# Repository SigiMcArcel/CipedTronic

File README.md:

#  feasibility study. Bicycle Speedometer
Hardware and software for measuring distance of a bike with a mobil phone.
The needed information will get thru the sine wave of the hub dynamo of the bike.
A hardware converts the sine wave to a TTL signal. 
A microcontroller counts the pulses
The mobil gets the data thru Bluetooth LE
A java app receive the Bluetooth LE data and shows the value on a GUI
The hardware must be simple and small for covering in a bicycle lamp.

#The Application
The microcontroller sends the 

count of pulses (distance), 
the count of pulses per second (velocity)
the count of pulses per second average
the count of pulses per second maximum
The count of pulses will save in the microcontrollers EEPROM

The Android App calculates the informations to Km/h and Km with settings like pulses per revolution and wheel radius,
this data will show in the GUI.

In the first Version i implemented the nordic UART Service and send and receive the data as string.
In the further versions i used a custom service and characteristics to exchange the data.So i spent code and was more comfortable to handle it 

The next idea is to use the standard Bluetooth LE service "Cycling Speed and Cadence" to exchange the data.
So i can use my speedometer with other android Apps.
Therfore i have to reimplement the the pulse measuring.

further steps are :
- Porting the software to a seed XIAO ESP32C3 is lot smaller and has akku load functions
- Combine the hardware with LED Lightning and Supercaps
- extend the android app with "Tours" functionality. So i can set several tours.

##Hardware Komponents
ATMEGA 32u4 Arduino Leonard0
Adafruit nrf80001 breakout
Samsung X-Cover Pro Smartphone Android SDK 30

#Developer Tools
Microchip studio for ATMEGA 32u4
Android studio for Android App developing
LT Spice for developing the Converter Hardware

## Hardware for pulse converting
The big Problem is to handle the voltage on unloaded state.
The voltage can gos up to > 20 Volts.

I'm still looking for a good and sinmplesolution for this problem

##Software
###Microcontroller
Project : CipedTronicMCU
The Software uses fololowing sources:
the nordic nrf80001 sdk
The USB CDC from J. Fiene & J. Romano https://github.com/PennRobotics/acrobot 

USBSerial:
For debugging i implemented a Modul for receive and send string and chars thru the usb interface of the ATMEGA 32u4.
Therfore i'm using the USBDCD source.

Bluetooth LE:
The Atmega 32u4 communicate thru SPI with the Bluetooth LE Breakout.
In the modul BLE.cpp all needed step are implemented for using the breakout.
The nordic sdk includes the necessary functions.
BLE.cpp is written in c++ for compatibility to the nordic sdk.

Evaluate the sine waves of the hub dynamo:
For that i use the counter 1 of the Atmega 32u4. it is count the pulses.
For prevent the overflow after 16 Bit, the software adds the actual counter value to a 32 bit variable and deletes the counter.
Every second the software checks the count of pulses since last call ang gives the count of pulses per second (Counter.c ,Timer.c)

maximum km's:
(Unloaded)
wheel radius = 37 cm, pulses per revolution = 18
circumference per revolution = 2 * 0,00037 kilometers * pi =    0,00232477856 kilometers
pulses per km = 1/0,00232477856 * 18 = 7742 Pulses
or 0,12915436 meters per puls

u32Bit =  4294967295 /7742 = 554761 km. (less than i thought,may be i need a u64Bit Integer)

accuracy:
depends on tire pressure and wight.
Loaded ->
Assumed 4,5 Bar pressure and 70 kg weight a different of 5 mm
circumference per revolution = 2 * 0,000365 kilometers * pi =    0,00229336263 kilometers
pulses per km = 1/0,00229336263 * 18 = 7 848 Pulses
or  0,12740903 meters per pulse									 
unloaded <-> loaded ->
6 Pulses -> 76 cm

almost a metre per kilometre. its a lot !!
But I found a test of gps tracker on Internet. Result : Real distance 5Km , gps tracker 5,14 km.
the speedometer  calculates :  5 km -> 5 * 76 cm = 380 cm. Maybe better.

###Android App
The App is implemented as a Viewmodel Pattern.
The BLE part is implemented fully asynchron. 
Actually the BLE part is written as a singleton class. But it prepared for using as Android service.
The data exchange between class and Viewmodel works with events and livedata.
GUI:
The App consists three Fragments there's is collected as tabs.
Main and Datafragments :
- Shows the velocity and distance
- Resets the counter
Devicefragment:
- Searching and select cipedtronic devices
Settingsfragment:
- Sets wheel raduis and pulses per revolution

classes:
BLEDevice.java : Consist the BLE Stack with all needed functionality.
CipedTronicMCU.java : Opens BLE services,handle characteristics, calculate mcu data
PageViewModel.java : handles data exchange beetween Fragments, starts the MCU/BLE Part

SectionsPagerAdapter.java : Handles Tabs and Fragments
DataFragment.java : The data GUI
DeviceFragment.java : The device search fragment
SettingsFragment.java : The settings fragment

#Branches:
##main
BLE Uart Version of Cipedtronic
##BLENonUart
 the CUstom and standard service

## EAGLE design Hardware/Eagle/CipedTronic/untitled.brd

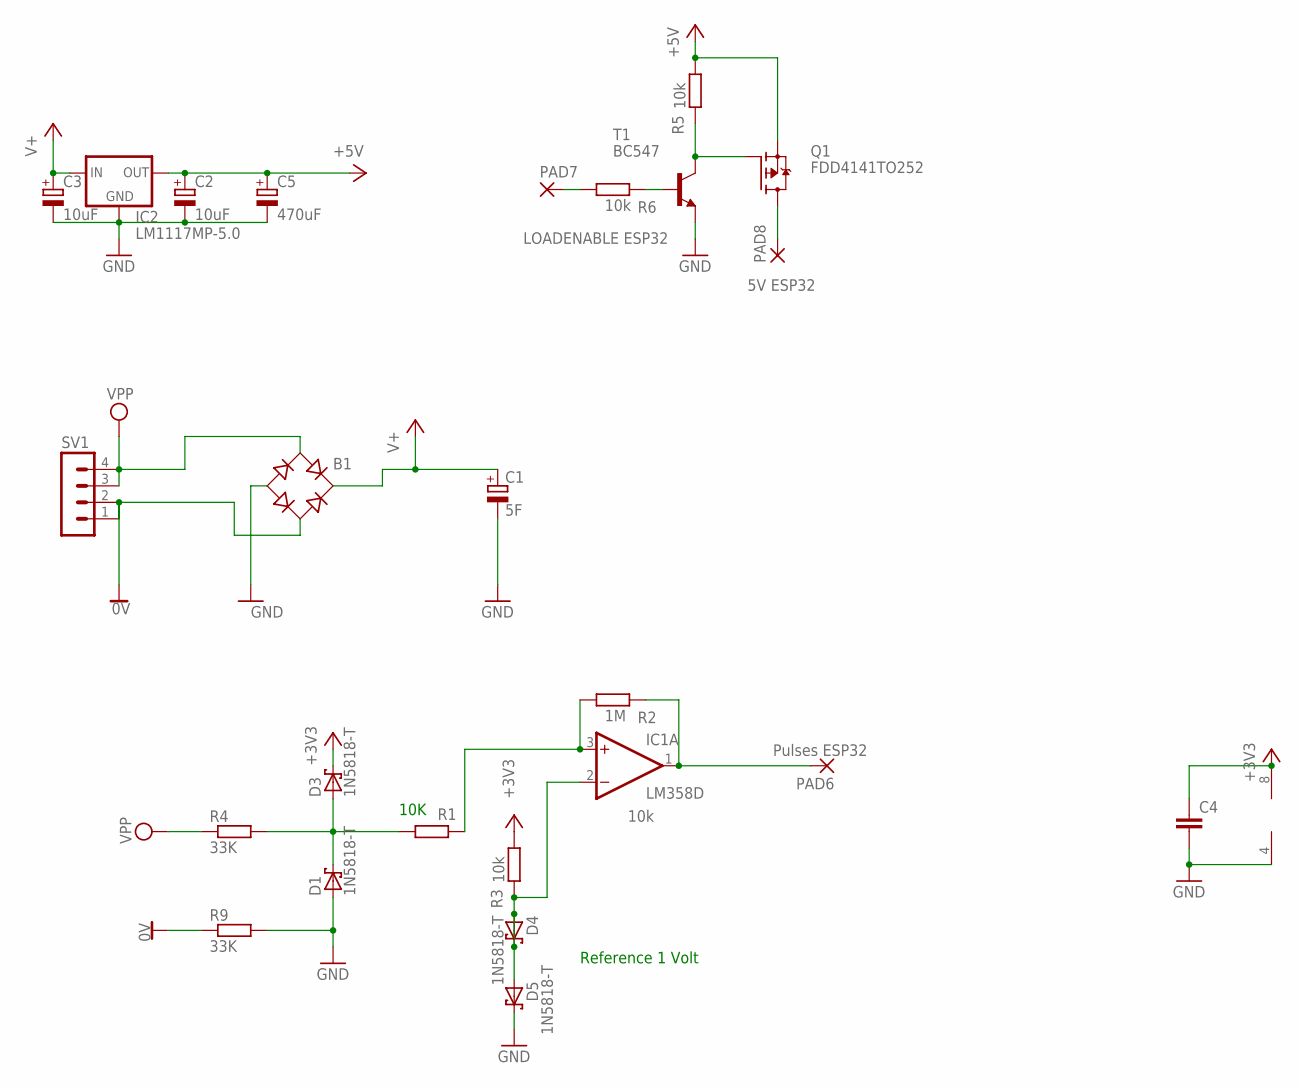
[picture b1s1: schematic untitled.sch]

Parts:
B1: B-DIL
C1: 5F; E2,5-6E
C2, C3: 10uF; E2,5-6E
C4: C-EU050-024X044; C050-024X044
C5: 470uF; E2,5-6E
D1, D3, D4, D5: 1N5818-T; DO41-7.6
IC1: LM358D; SO08
IC2: LM1117MP-5.0; SOT223
PAD6: Pulses ESP32; 2,15/1,0
PAD7: LOADENABLE ESP32; 2,15/1,0
PAD8: 5V ESP32; 2,15/1,0
Q1: FDD4141TO252; TO252
R1, R3, R5, R6: 10k; 0204V
R2: 1M; 0204V
R4, R9: 33K; 0204V
SV1: MA04-1
T1: BC547; TO92

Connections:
0V: B1.AC2, R9.1, SV1.1, SV1.2
+3V3: B1.+, C1.+, C4.1, D3.C, IC1.8 (V+), R3.1
+5V: C2.+, C5.+, IC2.2 (OUT), IC2.4 (OUT), Q1.2 (S), R5.1
GND: B1.-, C1.-, C2.-, C3.-, C4.2, C5.-, D1.A, D5.C, IC1.4 (V-), IC2.1 (GND), R9.2, T1.1 (E)
unnamed: IC1.1 (OUT), PAD6.1, R2.2
unnamed: PAD7.1, R6.1
unnamed: R6.2, T1.2 (B)
unnamed: IC1.3 (+IN), R1.1, R2.1
unnamed: D4.A, D4.C, D5.A, IC1.2 (-IN), R3.2
unnamed: Q1.1 (G), R5.2, T1.3 (C)
unnamed: PAD8.1, Q1.3 (D)
unnamed: D1.C, D3.A, R1.2, R4.2
V+: C3.+, IC2.3 (IN)
VPP: B1.AC1, R4.1, SV1.3, SV1.4

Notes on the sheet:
10K
Reference 1 Volt

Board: 2 copper layers, 25 parts (0 on the bottom side), 14 nets, no tracks yet.

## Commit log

2022-06-13 Initial request
2022-06-14 Android App: - Settings page added - Tour page added - Bugfix crash in timer run()
2022-06-23 - Changed to atmega32u4 - USB CDC added - Timer calibrated
2022-08-27 Changes for testing on newer bike (Dynamo has 18 Pulses) testing and improving
2022-10-02 missed file added (usb,eeprom routines)
2022-10-02 missing files added
2022-11-24 BLE: nrf8001 lib and Prozess added
2022-11-27 New UI for cipedtronic
2022-11-27 Bluetooth LE added
2022-12-11 - Bluetooth LE added - Protocoll extendend
2022-12-11 -BLE lib added
2022-12-11 missing File added
2022-12-11 - Viewmodel implemented - Tests with BLE
2022-12-27 Add missing hedaer file
2022-12-27 Better protocoll implemented Clean up Not tested too high memory usage. has to be improved
2023-01-04 - rebuild the app without Serial service - cleanups - testing with device
2023-01-04 missing new java files added
2023-01-07 pre rebuild
2023-01-08 big refactoring
2023-01-08 Great refactoring and simplifying of the Bluetooth part. Changing namespace cleanup
2023-01-08 Error handling while invalid Bluetooth addresses fixed. SettingsFragment : Bluetooth address must be read only Settings -> Changes will write immediately to CipedtronicMCU class Device Fragment -> Ch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
2023-01-15 cleanup documentation
2023-01-15 cleanups
2023-01-15 Error handling
2023-01-15 add disclaimer delete not necessary files
2023-01-15 revert
2023-02-13 migration to seed xaio esp32
2023-02-22 Cipedtronic with esp32
2023-02-26 Rename sketch Extend Timer Add namespace
2023-04-09 battery load functionality Radius distance sensor
2023-04-09 battery load functions distance sensor improved pulse formatting
2023-04-15 States as picture bluetooth handling improved
2023-04-15 Powersave handling save data in RTC RAM Info characteristic
2023-04-16 Wrong Error
2023-04-16 tests and fixes
